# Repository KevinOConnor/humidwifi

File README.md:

This is an experimental pcb design for a battery powered wireless
humidity, temperature, and pressure sensor. It uses an esp32 wifi chip
along with a bme280 sensor.

This is an experiment. There is no support for this project.

There is some information on the pcb design in the
[pcb document](docs/PCB.md).

There is some information on building the firmware in the
[firmware document](docs/Firmware.md).

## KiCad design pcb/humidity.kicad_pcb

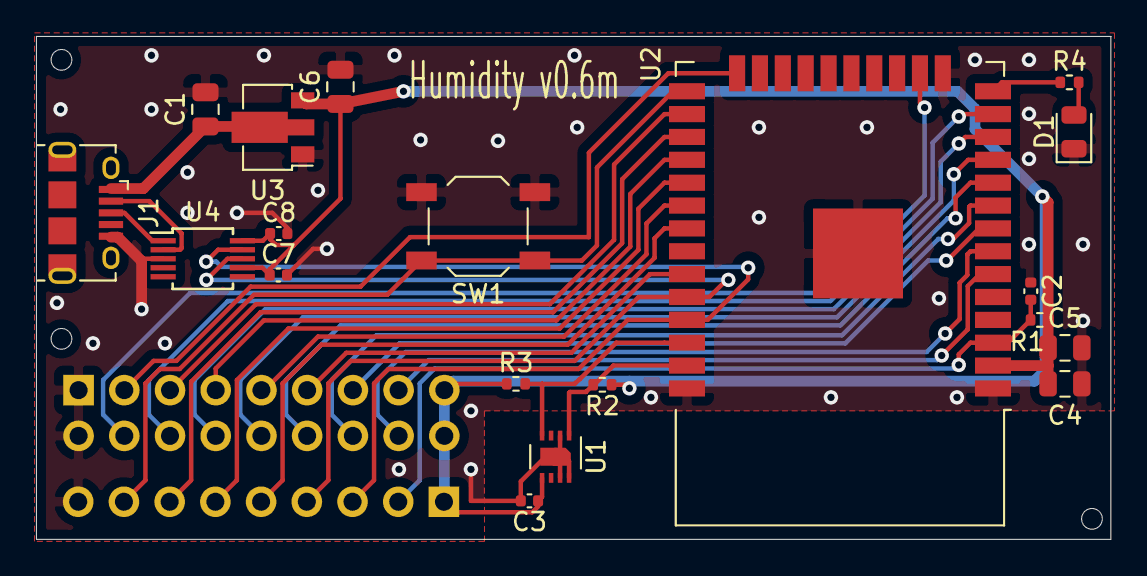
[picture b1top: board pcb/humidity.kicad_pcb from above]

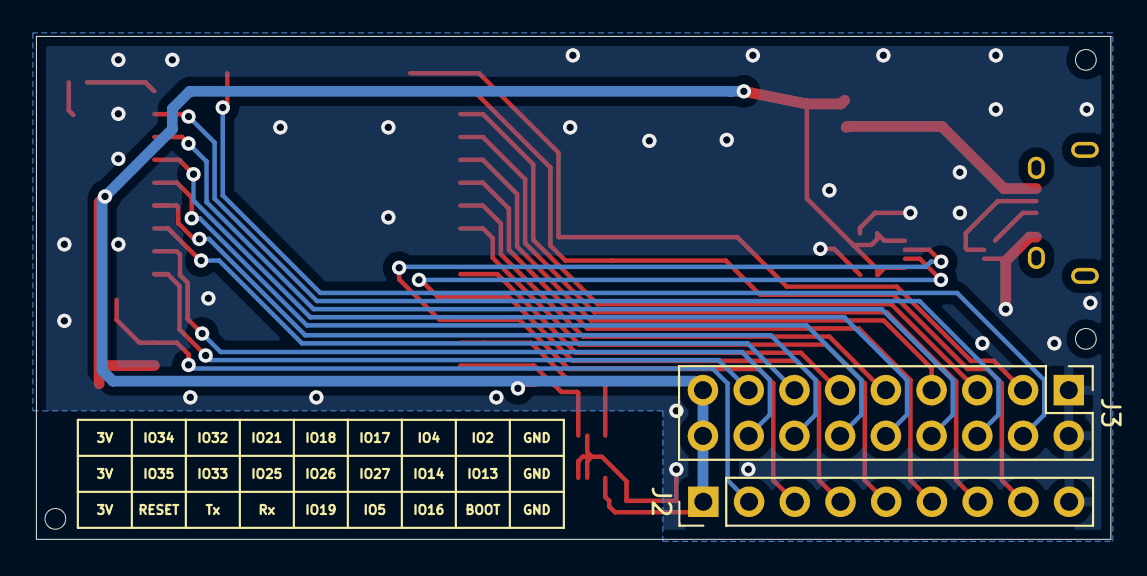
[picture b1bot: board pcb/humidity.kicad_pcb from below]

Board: 2 copper layers, 59.7 x 27.9 mm, 24 parts (2 on the bottom side), 30 nets.

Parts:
C1, C4, C6: 10uF; C_0805_2012Metric
C2, C3, C7, C8: 100nF; C_0402_1005Metric
C5: 100nF; C_0805_2012Metric
D1: Red LED; LED_0805_2012Metric
H1, H2, H3: ToolingHole; tooling_hole
J1: USB_B_Micro; USB_Micro-B_Amphenol_10118194_Horizontal
J2: Conn_01x09; PinHeader_1x09_P2.54mm_Vertical
J3: Conn_02x09_Odd_Even; PinHeader_2x09_P2.54mm_Vertical
R1: 10K Ohm; R_0402_1005Metric
R2, R3: 4.7K Ohm; R_0402_1005Metric
R4: 100 Ohm; R_0402_1005Metric
SW1: SW_Push; SW_SPST_TL3342
U1: SHT31-DIS; Sensirion_DFN-8-1EP_2.5x2.5mm_P0.5mm_EP1.1x1.7mm
U2: ESP32-WROOM-32
U3: HT7833-1-SOT89; SOT-89-3
U4: CH340E; MSOP-10_3x3mm_P0.5mm

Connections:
+BATT: C3.1, C4.1, C5.1, C6.1, C7.1, C8.1, J2.1, J3.17, J3.18, R1.1, R2.1, R3.1, U1.5, U2.2, U3.3, U4.7, U4.10
BOOT: J2.8, SW1.1, U2.25
GND: C1.2, C2.2, C3.2, C4.2, C5.2, C6.2, C7.2, C8.2, D1.1, J1.5, J2.9, J3.1, J3.2, SW1.2, U1.2, U1.7, U1.8, U1.9, U2.1, U2.15, U2.38, U2.39, U3.1, U4.3
IO2: J3.3, U2.24
IO4: J3.5, U2.26
IO5: J2.6, U2.29
IO13: J3.4, U2.16
IO14: J3.6, U2.13
IO16: J2.7, U2.27
IO17: J3.7, U2.28
IO18: J3.9, U2.30
IO19: J2.5, U2.31
IO21: J3.11, U2.33
IO25: J3.12, U2.10
IO26: J3.10, U2.11
IO27: J3.8, U2.12
IO32: J3.13, U2.8
IO33: J3.14, U2.9
IO34: J3.15, U2.6
IO35: J3.16, U2.7
LED: R4.1, U2.14
unnamed: C1.1, J1.1, U3.2
unnamed: D1.2, R4.2
RESET: C2.1, J2.2, R1.2, U2.3
RXD: J2.4, U2.34, U4.8
SCL: R3.2, U1.4, U2.36
SDA: R2.2, U1.1, U2.37
TXD: J2.3, U2.35, U4.9
USB_DM: J1.2, U4.2
USB_DP: J1.3, U4.1

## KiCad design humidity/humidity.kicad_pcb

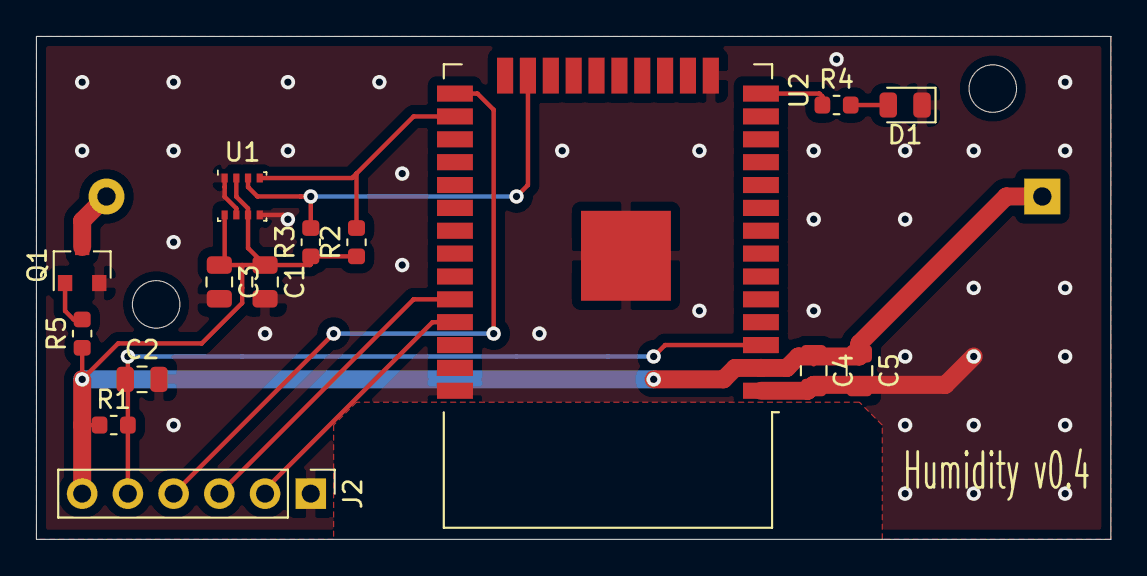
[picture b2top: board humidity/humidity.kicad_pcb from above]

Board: 2 copper layers, 59.7 x 27.9 mm, 16 parts (1 on the bottom side), 12 nets.

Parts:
C1, C2, C3, C5: 100nF; C_0805_2012Metric
C4: 10uF; C_0805_2012Metric
D1: Red LED; LED_0805_2012Metric
J1: Battery Holder; BatteryHolder_Keystone_2460_1xAA
J2: Conn_01x06; PinHeader_1x06_P2.54mm_Vertical
Q1: Q_NMOS_GSD; SOT-23
R1, R5: 10K; R_0603_1608Metric
R2, R3: 4K7; R_0603_1608Metric
R4: 0K1; R_0603_1608Metric
U1: BME280; Bosch_LGA-8_2.5x2.5mm_P0.65mm_ClockwisePinNumbering
U2: ESP32-WROOM-32

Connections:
+BATT: C1.1, C3.1, C4.1, C5.1, J1.1, J2.6, R1.1, R2.1, R3.1, R5.1, U1.2, U1.6, U1.8, U2.2
BOOT: J2.4, U2.25
GND: C1.2, C2.2, C3.2, C4.2, C5.2, D1.1, J2.1, Q1.2, U1.1, U1.5, U1.7, U2.1, U2.15, U2.38, U2.39
LED: R4.1, U2.14
unnamed: D1.2, R4.2
unnamed: J1.2, Q1.3
unnamed: Q1.1, R5.2
RESET: C2.1, J2.5, R1.2, U2.3
RXD: J2.3, U2.34
SCL: R2.2, U1.4, U2.26
SDA: R3.2, U1.3, U2.23
TXD: J2.2, U2.35

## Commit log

2019-12-27 Iniital commit
2020-01-01 Updates for Lifepo4 battery
    Use a 3.2V lifepo4 battery. This eliminates the need for a regulator.
    Remove the battery sensing circuit - the esp32 ADC should be able to
    sense VDD33 directly.
    Add an N-MOSFET on BATT- to protect against battery reverse polarity.
    Use 0805 LED size. Adjust LED resistor to 100ohm.
    Use wider traces for VBATT lines.
2020-01-02 Updates for JLCPCB
    Add LCSC part numbers (in case using JLCPCB to assemble).
    Use 0805 for the caps (as they're cheaper on JLCPCB).
    Add version information to silk screen. Add a warning about
    appropriate battery to the silk screen.
2020-01-02 Rework bme280 wire routing
    Simplify the wiring to the bme280. Improve the cap locations near the
    bme280.
    Add a 10K resistor to MOSFET gate (for ESD).
    Fix location of silk screen text.
2020-01-02 Further updates to n-mosfet
    Use AO3416 n-mosfet (which has ESD).
    Move n-mosfet to corner. Relocate the n-mosfet away from the edge and
    to reduce crowding.
    Minor wire routing improvements.
2020-02-23 case: Initial 3d printed case for sensor pcb
2020-05-16 pcb: Rename humidity/ directory to pcb/ directory
2020-05-16 fw: Add initial support for esp-idf based firmware
2020-05-16 docs: Add some initial overview documentation
2020-05-16 docs: Add a TODO document
2020-05-16 docs: Add "battery measurement" note to Firmware.md
2020-05-16 docs: Typo fix in Firmware.md
2020-05-17 readme: Reword readme slightly
2020-05-17 bme280: Avoid truncation of t_fine in conversion of temperature
2020-05-17 docs: Note gpio15 routing in todo
2020-05-17 scripts: Add graph_data.py graphing tool
2020-05-17 network: Convert to esp_netif interface
2020-05-17 battery: Use calibrated adc to voltage conversion
2020-05-18 network: Use dhcp to obtain the IP info even when using static IPs
2020-05-18 gitignore: Add fw/sdkconfig.old
2020-05-18 mqtt: Fix order of acknowledgments wrt clearing log data
2020-05-18 network: Convert REUSE_IP option to DHCP_LEASE_HOURS option
2020-05-20 mqtt: Disconnect when done
2020-05-23 deepsleep: Disable rom logging during deepsleep wakeup
2020-05-25 deepsleep: Do not call rtc_gpio_isolate()
    Calling rtc_gpio_isolate() is actually increasing the power
    consumption in deepsleep mode.
2020-05-25 deepsleep: Stop wifi on deepsleep
    Always call esp_wifi_stop() when entering deepsleep (the esp-idf docs
    indicate this should be done). Change network_disconnect() to just
    call esp_wifi_disconnect().
2020-05-25 CMakeLists: Change binary target to humidwifi.bin
2020-05-25 battery: Use simple scale/offset calculation
    Don't use the esp_adc_cal component and instead use configurable scale
    and offset settings to calibrate battery measurements.
2020-05-27 bme280: Minor code movement
    Just code movement; no code changes.
2020-05-27 bme280: Pass full data array to bme280 calibration functions
2020-05-27 datalog: Mark datalog_type_s instances as static
2020-05-27 main: Minor code simplification
2020-05-28 docs: Add a new RPi_Flash.md document
2020-05-28 humcase: Updates to 3d printed case
    Add additional pcb guide protrusions. Add battery vent holes.
2020-06-03 docs: Fix pin assignment typo in RPi_Flash.md
2020-06-10 graph_data: Convert to python3
2020-06-22 graph_data: Improve handling of duplicates and out of order messages
2020-06-28 graph_data: Allow filtering data by a date range
2020-08-25 graph_data: Optimize date parsing
2020-08-26 deepsleep: Make sure to use 64bit math when calculating times
2020-08-26 graph_data: Fix timestamp calculation
    Commit 2a7ac7f8 changed the timestamp base, but failed to update the
    ts_base variable. Fix that.
2021-06-12 graph_data: Add support for charting time to upload
2021-07-16 pcb: Update pcb with new routing (pcb v0.6)
    Move esp32 chip to side of board to allow more space for other
    components.
    Move bme280 chip away from battery and do not extend the ground plane
    under it. This is intended to improve thermal isolation of the bme280
    chip.
    Route most unused micro-controller pins to 2.54mm pins that are
2021-07-16 docs: Update TODO document
    Update the todo document with changes since v0.6 pcb design.
2021-07-16 Kconfig: Change defaults for v0.6 pcb
    The latest PCB uses different pins for i2c and battery level checking.
2021-07-16 docs: Add PCB rendering of v0.6 pcb
2021-07-16 README: Add pictures of assembled board
2021-07-18 docs: Fix typo in PCB.md
2021-07-21 case: Updates to case
    Increase size of lid "dimple" to improve lid locking.
    Slightly reduce y dimensions to reduce overall case size.
    Align air holes and decrease their size.
    Minor syntax cleanups.
2021-07-21 docs: Rename docs/pics/ directory to docs/img/
2021-07-21 docs: Add a picture of the 3d printed case
2021-09-18 Add script to generate mosquitto_pub commands for MQTT discovery in Home Assistant.
2021-09-18 scripts: Add script to generate mosquitto_pub commands for MQTT discovery in Home Assistant. (#1)
2021-09-27 pcb: Update to use SHT-31 humidity chip
    Replace bme280 with sht31 humidity chip.
    Add jlcpcb tooling holes to the board.
    Save gerber files to pcb/out/ directory.
2021-09-27 pcb: Add mains powered variant of board
    Add usb-micro-b connector for power and comms.
    Add ams1117-3.3v regulator for power.
    Add ch340 chip for comms.
2021-09-28 pcb: Add footprint for a jlcpcb tooling hole
2021-09-28 pcb: WIP - convert to an ht7833 regulator
2021-11-11 docs: Update to use https://kicad.org/
2022-01-24 Set device hostname to the MQTT topic prefix
2022-02-09 network: Setup a default dhcp hostname based on mqtt topic
2022-02-09 calculate: Add helper script to calculate a battery scale
